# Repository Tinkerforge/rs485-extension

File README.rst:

RS485 Extension
===============

This repository contains the hardware design files.
The software is included in the Master Brick software
and can be found at https://github.com/Tinkerforge/master-brick

Repository Content
------------------

hardware/:
 * Contains KiCad project files and additionally schematics as PDF

datasheets/:
 * Contains datasheets for sensors and complex ICs that are used

Hardware
--------

The hardware is designed with the open source EDA Suite KiCad
(http://www.kicad.org). Before you are able to open the files,
you have to install the Tinkerforge kicad-libraries
(https://github.com/Tinkerforge/kicad-libraries). You can either clone
them directly in hardware/ or clone them in a separate folder and
symlink them into hardware/
(ln -s kicad_path/kicad-libraries project_path/hardware). After that you
can open the .pro file in hardware/ with KiCad and from there view and
modify the schematics and the PCB layout.

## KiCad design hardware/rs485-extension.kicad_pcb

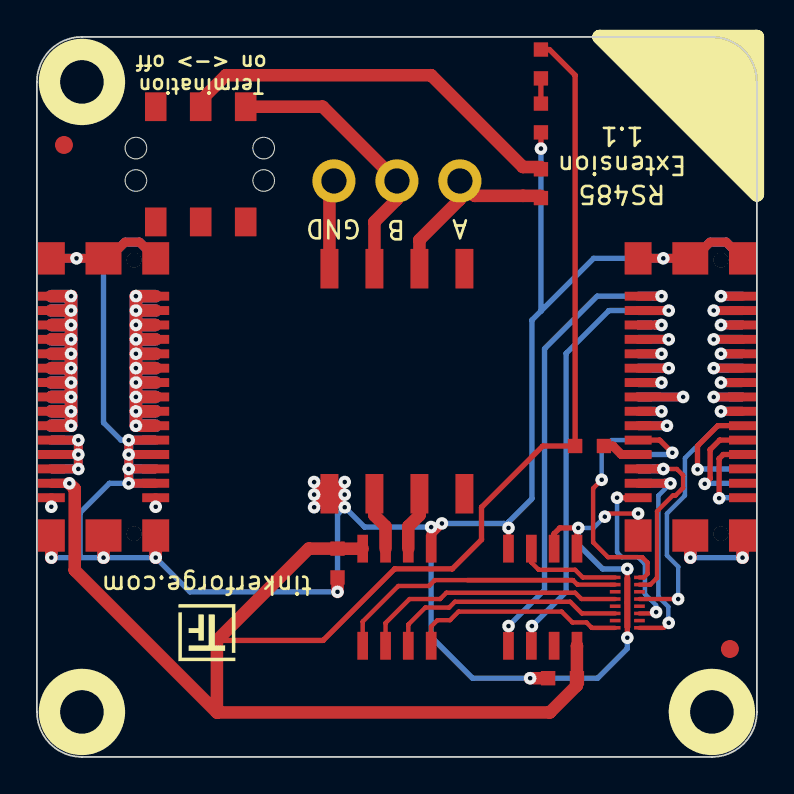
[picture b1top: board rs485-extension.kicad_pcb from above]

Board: 2 copper layers, 40.0 x 40.0 mm, 27 parts (0 on the bottom side), 48 nets.

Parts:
C1, C2: 100nF; C0603
D1: LED; D0603
FILTER1: Filter-8x; DFN16-33x135
Fiducial_Mark: VAL**; Fiducial_Mark
Fiducial_Mark#2, Fiducial_Mark#3, Fiducial_Mark#4: VAL**; Fiducial_Mark
J1, J3: STACK-UP-HIGH; BTB08-ACS-TOP
J2, J4: STACK-DOWN; BTB08-ACS-BTM
K1: grey; OQ_3P
L1: WE-SL
R1: 120; R0603
R2, R3: 1k; R0603
Ref**: Val**; Logo_31x31
SW1: TER; SLIDE_SWITCH
U1: M24C64; SOIC8
U2: ADM3485; SOIC8
U3, U4, U5, U6: DRILL; DRILL_NP
VAL: WEEE_7mm
VAL#2: CE_5mm

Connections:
3V3: C1.1, C2.1, D1.1, J3.28, J4.28, R3.1, U1.8, U2.8
GND: C1.2, C2.2, FILTER1.EXP, J1.EP, J2.EP, J3.21, J3.23, J3.25, J3.27, J3.EP, J4.21, J4.23, J4.25, J4.27, J4.EP, L1.1, R2.2, U1.1, U1.2, U1.4, U2.5
unnamed: D1.2, R2.1
unnamed: FILTER1.1, U1.3
unnamed: FILTER1.2, U2.1
unnamed: FILTER1.4, U2.2
unnamed: FILTER1.6, U2.3
unnamed: FILTER1.8, U2.4
unnamed: J1.1, J2.1
unnamed: J1.3, J2.3
unnamed: J1.5, J2.5
unnamed: J1.6, J2.6
unnamed: J1.7, J2.7
unnamed: J1.8, J2.8
unnamed: J1.9, J2.9
unnamed: J1.10, J2.10
unnamed: J1.11, J2.11
unnamed: J1.12, J2.12
unnamed: J1.13, J2.13
unnamed: J1.14, J2.14
unnamed: J1.15, J2.15
unnamed: J1.16, J2.16
unnamed: J1.17, J2.17
unnamed: J1.18, J2.18
unnamed: J1.19, J2.25
unnamed: J1.20, J2.20
unnamed: J1.21, J2.27
unnamed: J1.22, J2.24
unnamed: J1.23, J2.29
unnamed: J1.24, R3.2
unnamed: J3.1, J3.3, J3.5, J3.7, J3.9, J3.11, J3.13, J3.15, J3.17, J3.19, J4.1, J4.3, J4.5, J4.7, J4.9, J4.11, J4.13, J4.15, J4.17, J4.19
unnamed: J3.2, J3.4, J3.6, J3.8, J3.10, J3.12, J3.14, J3.16, J3.18, J3.20, J4.2, J4.4, J4.6, J4.8, J4.10, J4.12, J4.14, J4.16, J4.18, J4.20
unnamed: J3.22, J3.24, J3.26, J4.22, J4.24, J4.26
unnamed: J3.29, J4.29
unnamed: J3.30, J4.30
unnamed: K1.1, L1.6, R1.1
unnamed: K1.2, L1.7, SW1.1
unnamed: K1.3, L1.8
unnamed: L1.2, U2.7
unnamed: L1.3, U2.6
unnamed: R1.2, SW1.2
RXD: FILTER1.15, J1.26, J2.26
RXE: FILTER1.13, J2.19
SCL: J1.4, J2.4, U1.6
SDA: J1.2, J2.2, U1.5
SELECT: FILTER1.16, J2.22
TXD: FILTER1.9, J1.28, J2.28
TXE: FILTER1.11, J1.30, J2.30

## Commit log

2016-09-29 drc check executed
2017-08-03 Add 3d information (tbc)
2017-09-15 Add 3d information (final)
2017-09-15 Add 3d model (*.step & *.FCStd)
2018-02-20 Add .gitignore
2018-02-20 Cleanup KiCad libraries config
    Ensure LibDir=kicad-libraries and LibName1=tinkerforge.
    Remove special library.
2021-10-25 Update KiCad link
    https://www.kicad.org/blog/2021/10/Avoid-links-to-former-kicad-domain/

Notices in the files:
hardware/rs485-extension.kicad_pcb:
Licensed under CERN OHL v.1.1
Copyright (©) 2015, B.Nordmeyer
Copyright Tinkerforge GmbH 2015.
This documentation describes Open Hardware and is licensed under the
CERN OHL v. 1.1.
